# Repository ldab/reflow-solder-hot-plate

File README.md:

# reflow-solder-hot-plate
 USB-C powered, esp32s3 based, hot plate

## Before anything else:

:exclamation: :boom:

Make sure you understand the risks involved on this project as you will be dealing with high temperatures and high-ish voltages.

It is important that the power supply used is able to supply enough current, otherwise it will crash, if you got the board from me it should be fine, otherwise adjust the values on `lib/temp_control/temp_control.h`

### TODO

* Save readings on a vector so it reloads the graph in case you leave the webpage;
* Websocket terminal;
* Use the button to trigger reflow;

### Main CPU

I used the the following board because that is what I had on my drawer:

### Reflow profile

It takes 3x temperature "profiles" as arguments, just to keep it simple

### Duty cycle and Supply current

With a duty cycle of 78% (PWM is inverted), it results in 22% of the total power and at 20V it should draw ~2.16A

https://tinyurl.com/2pvo2wyf

### Known issues

* Because of the mosfet logic and high current, when plugged to the computer, the USB-A port will probably struggle to deliver power and will rover around 3.6V, which is not enough to feed the Buck-Converter, that will result in the ESP32 to not wake up and the Mosfet will be constantly ON :exclamation: :exclamation: :exclamation:

* For the reason mentioned above, it need to be programed via RX/TX test points under the board;

* RX connects to RX and TX connects to TX :disappointed:

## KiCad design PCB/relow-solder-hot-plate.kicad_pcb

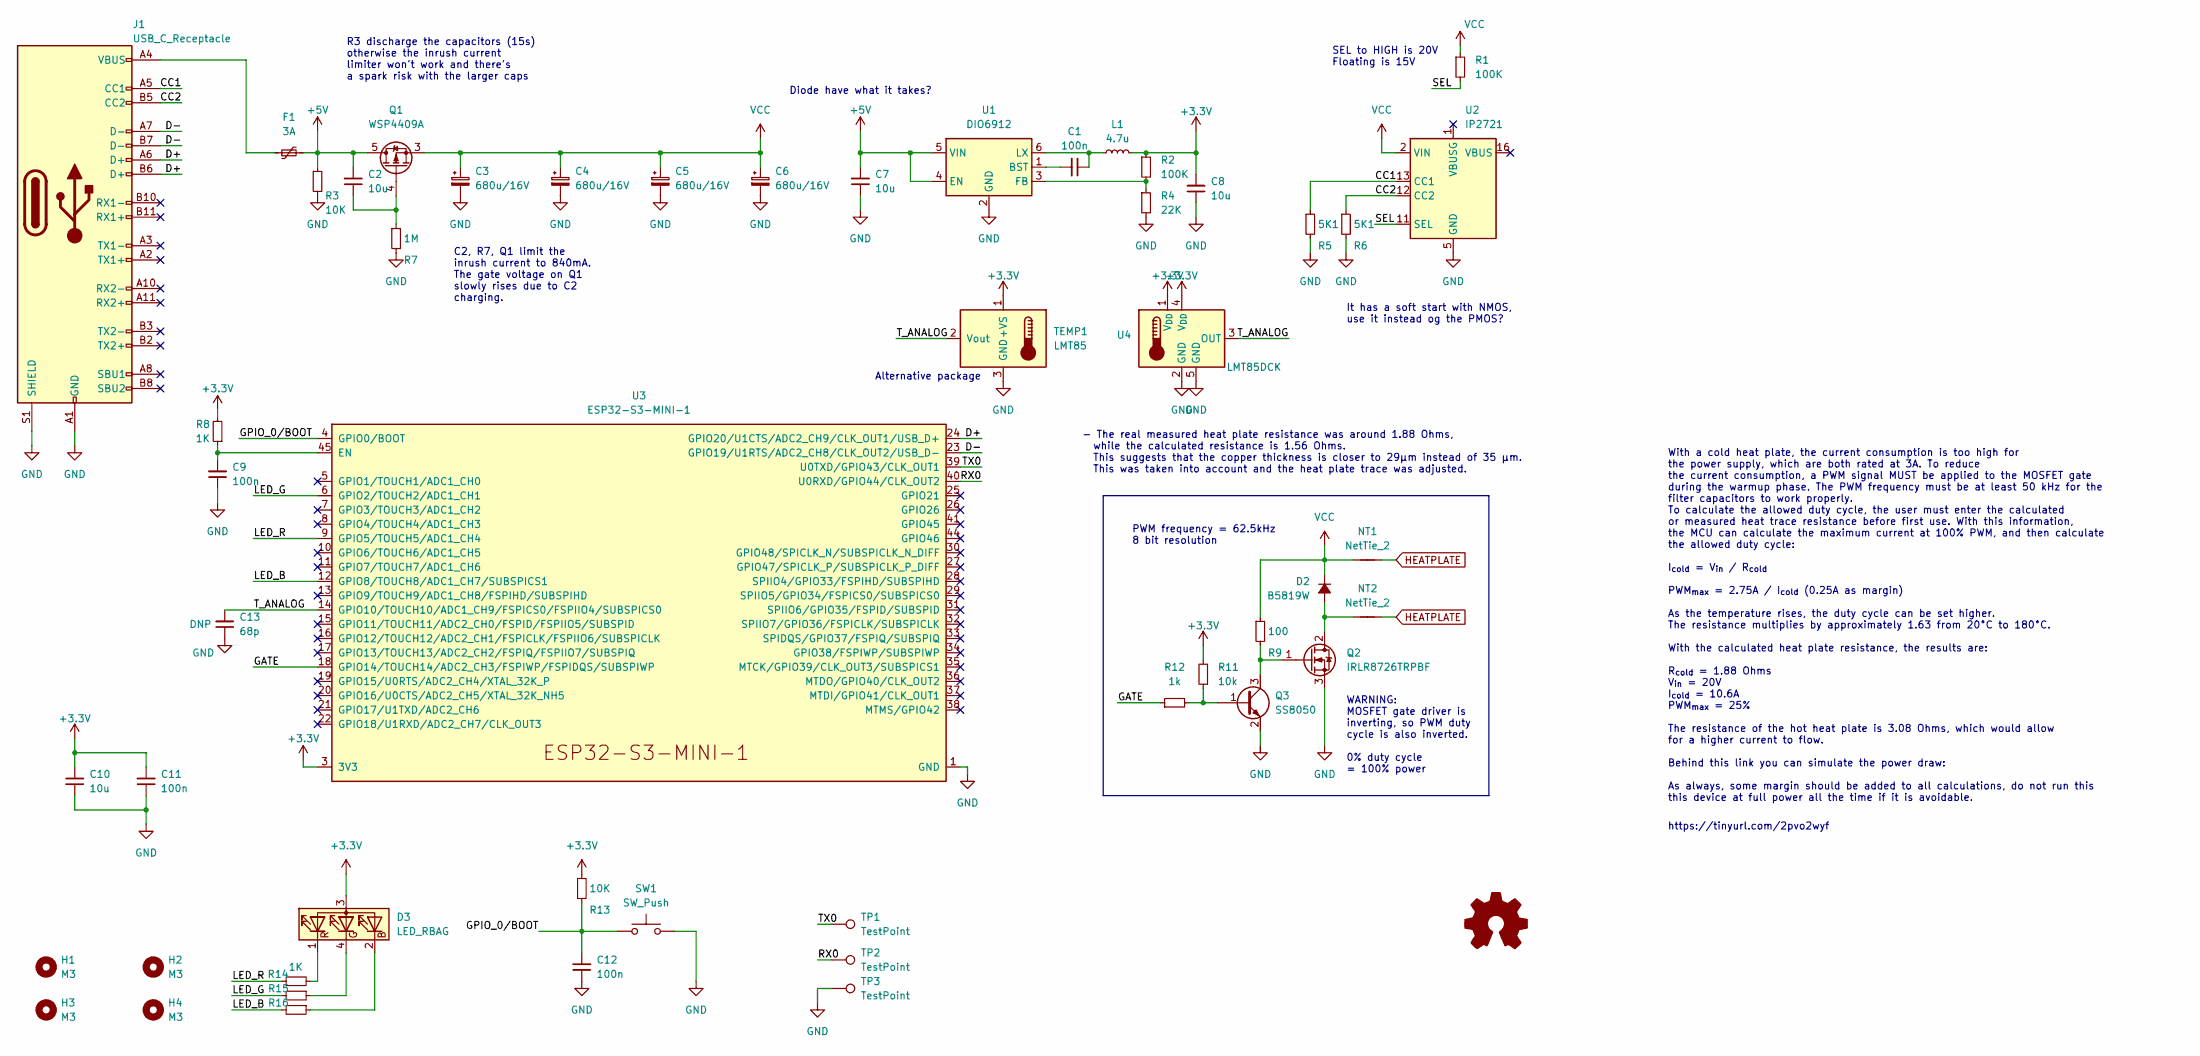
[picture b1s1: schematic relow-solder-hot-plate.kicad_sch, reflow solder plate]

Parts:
C1, C9, C11, C12: 100n; C_0603_1608Metric; LCSC C338036
C2, C7, C8, C10: 10u; C_0603_1608Metric; LCSC C87152
C3, C4, C5, C6: 680u/16V; CP_Radial_D8.0mm_P3.50mm; LCSC Part Number C88760
C13: 68p; C_0603_1608Metric; LCSC C162261
D2: B5819W; D_SOD-123; LCSC Part Number C64885
D3: LED_RBAG; LED_Cree-PLCC4_2x2mm_CW; LCSC C108793
F1: 3A; Fuse_2920_7451Metric; LCSC Part Number C841188
H1, H2, H3, H4: M3; MountingHole_3.2mm_M3; LCSC Part Number C551332
J1: USB_C_Receptacle; USB_C_Receptacle_HRO_TYPE-C-31-M-12
L1: 4.7u; L_1210_3225Metric; LCSC C90319
LOGO1: Logo_Open_Hardware_Small; OSHW-Logo2_7.3x6mm_SilkScreen
NT1, NT2: NetTie_2; NetTie-2_SMD_Pad1.3mm
Q1: WSP4409A; SOIC-8_3.9x4.9mm_P1.27mm; LCSC Part Number C2880527
Q2: IRLR8726TRPBF; TO-252-2; LCSC Part Number C81137
Q3: SS8050; SOT-23; LCSC Part Number C444722
R1, R2: 100K; R_0603_1608Metric; LCSC C2907088
R3, R13: 10K; R_0603_1608Metric; LCSC C17414
R4: 22K; R_0603_1608Metric; LCSC C2907128
R5, R6: 5K1; R_0603_1608Metric; LCSC C14677
R7: 1M; R_0603_1608Metric
R8, R14, R15, R16: 1K; R_0603_1608Metric; LCSC C384295
R9: 100; R_0603_1608Metric; LCSC C14677
R11: 10k; R_0603_1608Metric; LCSC Part Number C17414
R12: 1k; R_0603_1608Metric; LCSC Part Number C384295
SW1: SW_Push; SW_PUSH_6mm_H4.3mm; LCSC C499289
TEMP1: LMT85; TO-92_Inline; LCSC Part Number C75856
TP1, TP2, TP3: TestPoint; TestPoint_Pad_D1.5mm
U1: DIO6912; SOT-23-6; LCSC C444642
U2: IP2721; TSSOP-16_4.4x5mm_P0.65mm; JLCPCB basic part n
U3: ESP32-S3-MINI-1; LCSC C2913206
U4: LMT85DCK; SOT-353_SC-70-5

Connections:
+3V3: C8.2, C10.2, C11.2, D3.3 (A), L1.2, R2.1, R8.2, R11.2, R13.1, TEMP1.1 (+VS), U3.3 (3V3), U4.1 (V_{DD}), U4.4 (V_{DD})
+5V: C2.2, C7.2, F1.2, Q1.5 (D), Q1.6 (D), Q1.7 (D), Q1.8 (D), R3.1, U1.4 (EN), U1.5 (VIN)
/CC1: J1.A5 (CC1), R5.1, U2.13 (CC1)
/CC2: J1.B5 (CC2), R6.1, U2.12 (CC2)
/D+: J1.A6 (D+), J1.B6 (D+), U3.24 (GPIO20/U1CTS/ADC2_CH9/CLK_OUT1/USB_D+)
/D-: J1.A7 (D-), J1.B7 (D-), U3.23 (GPIO19/U1RTS/ADC2_CH8/CLK_OUT2/USB_D-)
/GATE: R12.1, U3.18 (GPIO14/TOUCH14/ADC2_CH3/FSPIWP/FSPIDQS/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)
/GPIO_0/BOOT: C12.2, R13.2, SW1.1, U3.4 (GPIO0/BOOT)
/LED_B: R16.2, U3.12 (GPIO8/TOUCH8/ADC1_CH7/SUBSPICS1)
/LED_G: R15.2, U3.6 (GPIO2/TOUCH2/ADC1_CH1)
/LED_R: R14.1, U3.9 (GPIO5/TOUCH5/ADC1_CH4)
/RX0: TP2.1, U3.40 (U0RXD/GPIO44/CLK_OUT2)
/SEL: R1.2, U2.11 (SEL)
/TX0: TP1.1, U3.39 (U0TXD/GPIO43/CLK_OUT1)
/T_ANALOG: C13.2, TEMP1.2 (Vout), U3.14 (GPIO10/TOUCH10/ADC1_CH9/FSPICS0/FSPIIO4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), U4.3 (OUT)
GND: C3.2, C4.2, C5.2, C6.2, C7.1, C8.1, C9.1, C10.1, C11.1, C12.1, C13.1, J1.A1 (GND), J1.A12 (GND), J1.B1 (GND), J1.B12 (GND), J1.S1 (SHIELD), Q2.3 (S), Q3.2 (E), R3.2, R4.2, R5.2, R6.2, R7.2, SW1.2, TEMP1.3 (GND), TP3.1, U1.2 (GND), U2.5 (GND), U3.1 (GND), U3.2 (GND), U3.42 (GND), U3.43 (GND), U3.46 (GND), U3.47 (GND), U3.48 (GND), U3.49 (GND), U3.50 (GND), U3.51 (GND), U3.52 (GND), U3.53 (GND), U3.54 (GND), U3.55 (GND), U3.56 (GND), U3.57 (GND), U3.58 (GND), U3.59 (GND), U3.60 (GND), U3.61 (GND), U3.62 (GND), U3.63 (GND), U3.64 (GND), U3.65 (GND), U4.2 (GND), U4.5 (GND)
HEATPLATE: NT1.2, NT2.2
unnamed: D2.2 (A), NT2.1, Q2.2 (D)
unnamed: D3.2 (BK), R16.1
unnamed: D3.4 (GK), R15.1
unnamed: D3.1 (RK), R14.2
unnamed: F1.1, J1.A4 (VBUS), J1.A9 (VBUS), J1.B4 (VBUS), J1.B9 (VBUS)
unnamed: C2.1, Q1.4 (G), R7.1
unnamed: Q2.1 (G), Q3.3 (C), R9.2
unnamed: Q3.1 (B), R11.1, R12.2
unnamed: C1.2, U1.1 (BST)
unnamed: R2.2, R4.1, U1.3 (FB)
unnamed: C1.1, L1.1, U1.6 (LX)
unnamed: C9.2, R8.1, U3.45 (EN)
VCC: C3.1, C4.1, C5.1, C6.1, D2.1 (K), NT1.1, Q1.1 (S), Q1.2 (S), Q1.3 (S), R1.1, R9.1, U2.2 (VIN)

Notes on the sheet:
C2, R7, Q1 limit the inrush current to 840mA. The gate voltage on Q1 slowly rises due to C2 charging.
Alternative package
PWM frequency = 62.5kHz 8 bit resolution
With a cold heat plate, the current consumption is too high for the power supply, which are both rated at 3A. To reduce the current consumption, a PWM signal MUST be applied to the MOSFET gate during the warmup phase. The PWM frequency must be at least 50 kHz for the filter capacitors to work prope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
It has a soft start with NMOS, use it instead og the PMOS?
WARNING: MOSFET gate driver is inverting, so PWM duty cycle is also inverted. 0% duty cycle = 100% power
R3 discharge the capacitors (15s) otherwise the inrush current limiter won't work and there's a spark risk with the larger caps
https://tinyurl.com/2pvo2wyf
Diode have what it takes?
- The real measured heat plate resistance was around 1.88 Ohms, while the calculated resistance is 1.56 Ohms. This suggests that the copper thickness is closer to 29µm instead of 35 µm. This was taken into account and the heat plate trace was adjusted.
SEL to HIGH is 20V Floating is 15V

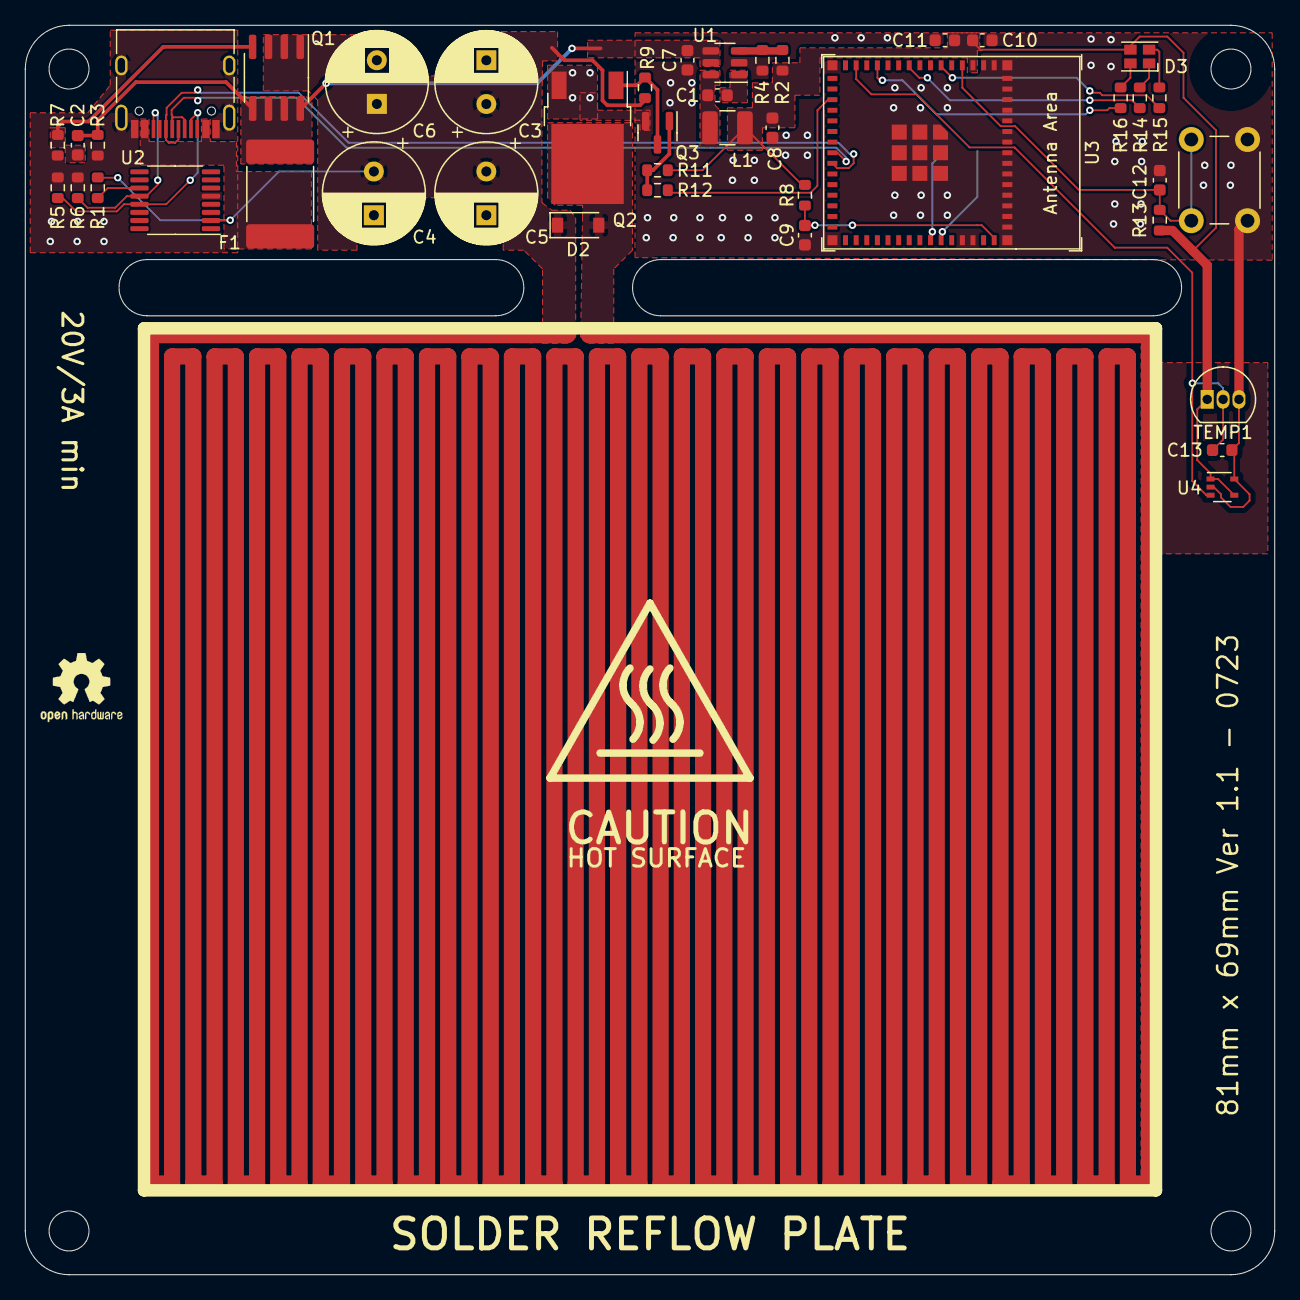
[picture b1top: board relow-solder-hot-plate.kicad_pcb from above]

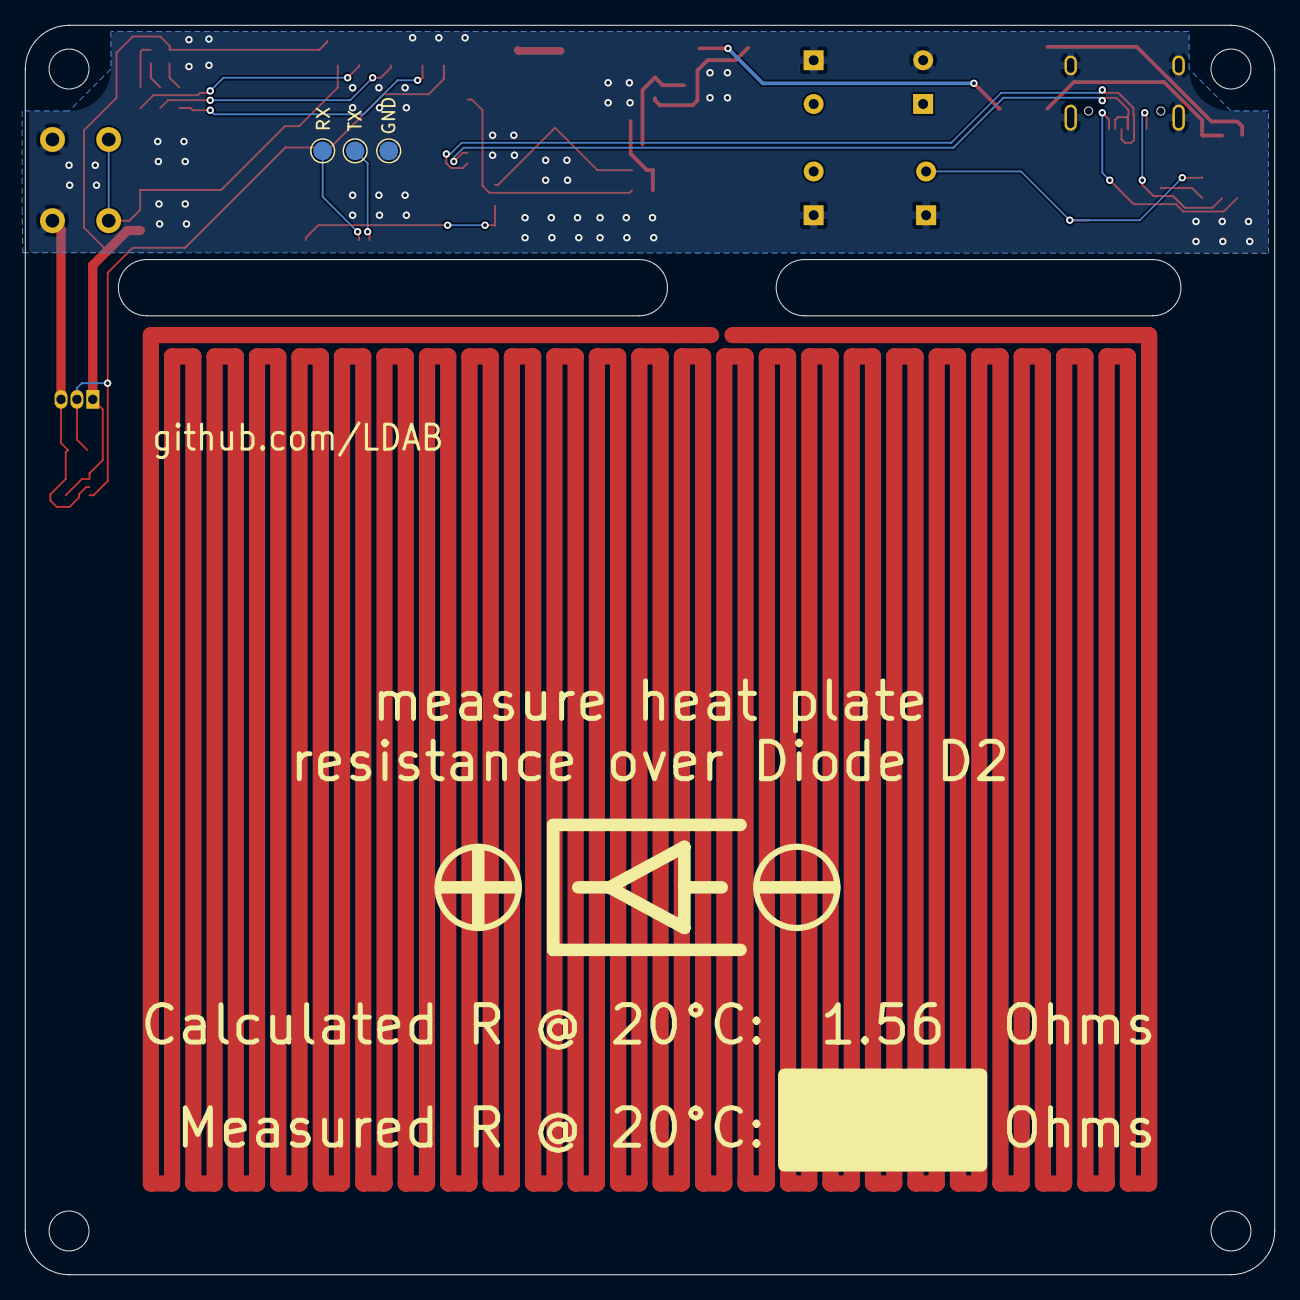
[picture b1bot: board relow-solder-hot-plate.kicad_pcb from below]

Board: 2 copper layers, 100.0 x 100.0 mm, 52 parts (3 on the bottom side), 30 nets.

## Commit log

2023-01-05 first draft
2023-01-06 simulation and few adjustments
2023-01-09 schematic release
2023-01-09 layout done
2023-01-09 BOM and schematic in pdf
2023-02-24 Hardware files (#1)
2023-02-24 FW draft
2023-02-24 web server
2023-02-24 draft gpios
2023-02-24 lmt85
2023-02-24 draft temp control
2023-02-25 dry run
2023-02-25 minor fix
2023-02-27 LEDs are active LOW
2023-02-27 inverted PWM
2023-02-27 captive portal and webserver
2023-02-28 Fix silkscreen and LMT85 footprint
2023-02-28 fix adc attenuation
2023-02-28 fix pwm frequency
2023-02-28 proto
2023-03-01 lmt85 fix
2023-03-07 create mdns task
2023-03-07 green led when connected
2023-03-07 reset leds, when color changes
2023-03-07 20V@2.25A power supply
2023-03-18 wet run
2023-03-19 fix mdns
2023-03-19 Proto (#2)
    * FW draft
    * web server
    * draft gpios
    * lmt85
    * draft temp control
    * dry run
2023-05-14 git tag
2023-05-14 get profile from web
2023-05-14 0.0.1 (#3)
    * git tag
    * ...
    * get profile from web
    * update readme
2023-05-14 prevent setpoint to increase too much
2023-05-14 restart at the end
2023-07-23 fix usb-c programmer
2023-07-23 cosmetic fix

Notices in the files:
README.md:
License: WTFPL
